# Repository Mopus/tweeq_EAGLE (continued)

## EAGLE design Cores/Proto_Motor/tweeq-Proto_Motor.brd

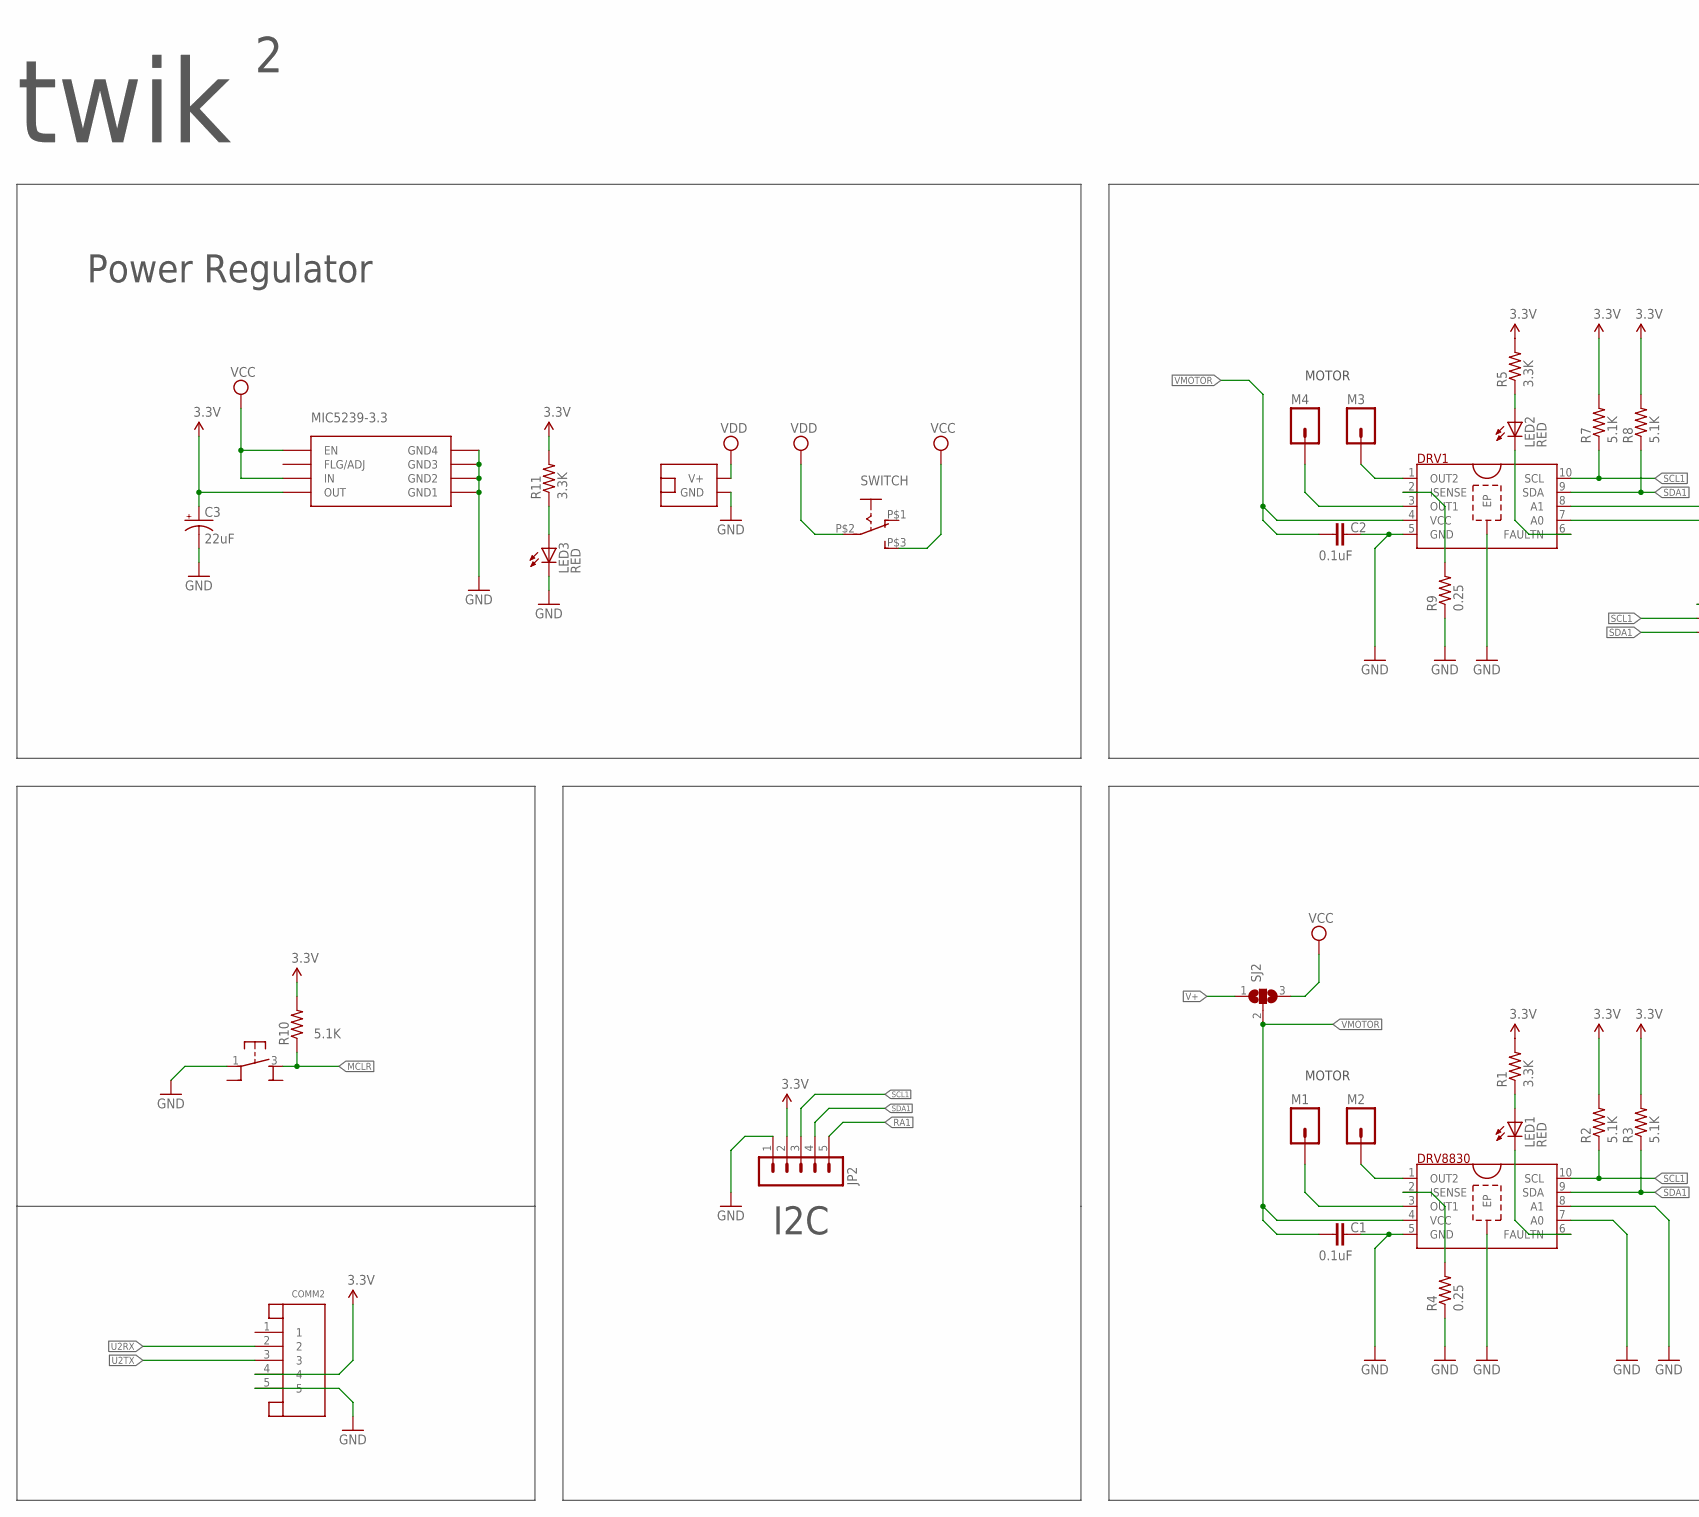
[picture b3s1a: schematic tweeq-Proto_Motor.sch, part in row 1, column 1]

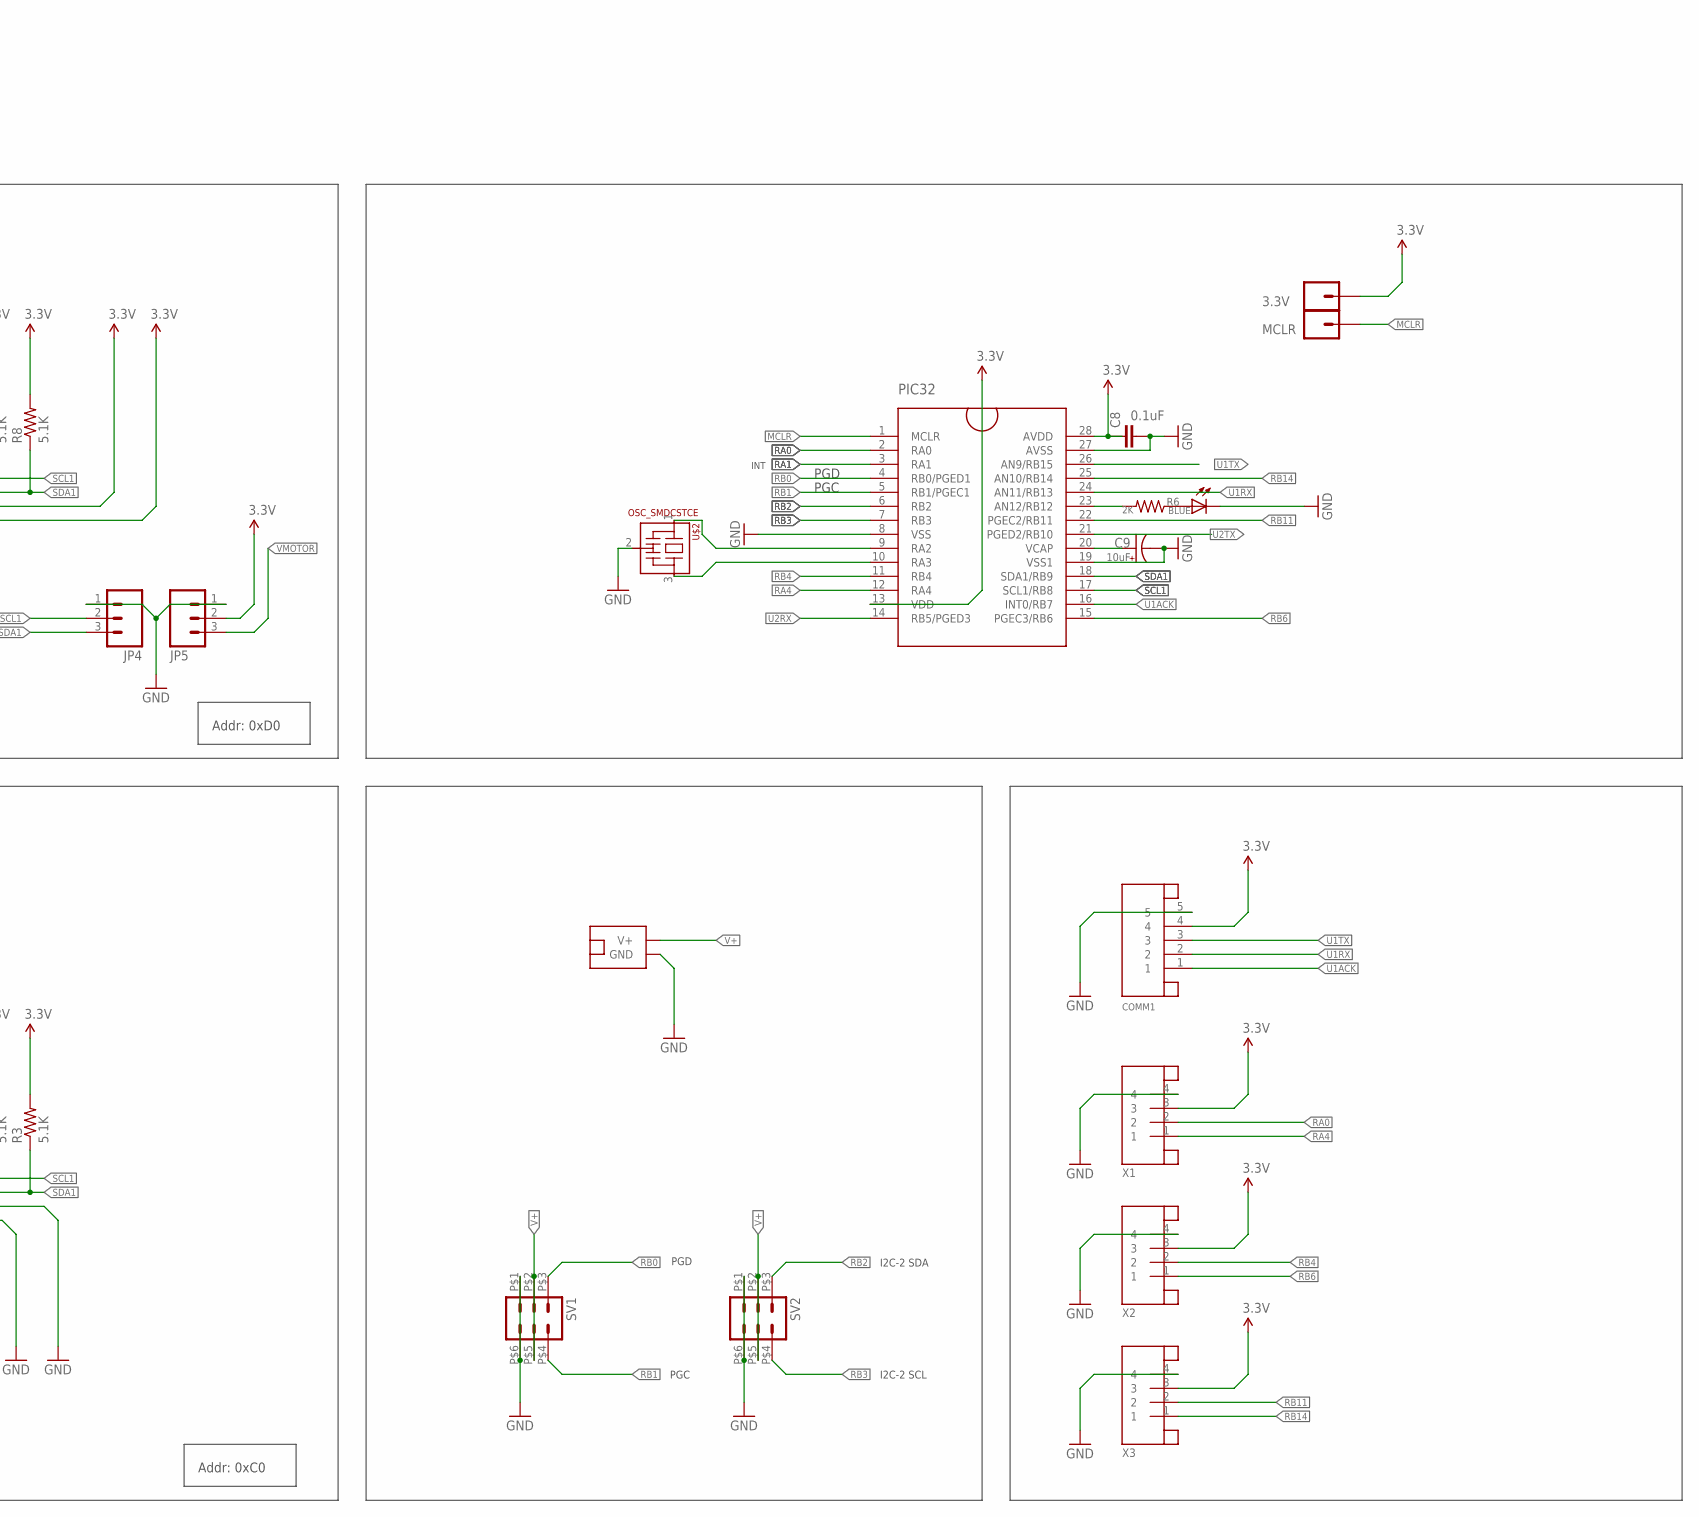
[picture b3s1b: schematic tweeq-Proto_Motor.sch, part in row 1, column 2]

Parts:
3.3V: M01; AISCUBE_1X01_TIGHTFITVIA
C1, C2, C8: 0.1uF; C0402K
C3: 22uF; SMC_B
C9: 10uF; A/3216-18R
COMM1, COMM2: JST-5PINSH; SH1.0-5PIN
DRV1, DRV8830: DRV8830DGQ; MSOP10_POWERPAD
JP2: M05-11.5MM-SMT; 1X05-1.5MM-SMT
JP4, JP5: M03/NS; 1X03_NS
LED1, LED2: RED; CHIPLED_0805
LED3: RED; CHIP-LED0805
M1, M2, M3, M4: M01SQ_NS; 1X01_SQ
MCLR: M01; AISCUBE_1X01_TIGHTFITVIA
MIC5239-3.3: MIC5239-MM; MSOP8
PIC32: PIC32MX_1XX_2XX; SSOP28
PIC_LED: BLUE; CHIP-LED0805
R1, R5, R11: 3.3K; R0402
R2, R3, R7, R8, R10: 5.1K; R0402
R4, R9: 0.25; R0402
R6: 2K; R0402
SJ2: JUMPER_SJ2W; JUMPER_SJ_2
SV1, SV2: M03-2EDGE_PAD; 2X03_EDGEPAD
SWITCH: SLIDE_SWITCH_SMALL
U$2: OSC_SMDCSTCE; CSTCE_RESONATOR_SMD
U$4: PB_MICRO_SMT; PB_SMT_3.5X3X2
U$9, U$10: POWER_CONN/PTH; POWER_CONN_PTH
X1, X2, X3: JST-4PINSH; SH1.0-4PIN

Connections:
3.3V: 3.3V.P$1, C3.+, C8.1, COMM1.4, COMM2.4, DRV1.7 (A0), DRV1.8 (A1), JP2.2, JP5.2, MIC5239-3.3.4 (OUT), PIC32.13 (VDD), PIC32.28 (AVDD), R1.2, R2.2, R3.2, R5.2, R7.2, R8.2, R10.2, R11.2, X1.3, X2.3, X3.3
GND: C1.2, C2.2, C3.-, C8.2, C9.-, COMM1.5, COMM2.5, DRV1.5 (GND), DRV1.EP, DRV8830.5 (GND), DRV8830.7 (A0), DRV8830.8 (A1), DRV8830.EP, JP2.1, JP4.1, JP5.1, LED3.C, MIC5239-3.3.5 (GND1), MIC5239-3.3.6 (GND2), MIC5239-3.3.7 (GND3), MIC5239-3.3.8 (GND4), PIC32.8 (VSS), PIC32.19 (VSS1), PIC32.27 (AVSS), PIC_LED.C, R4.1, R9.1, SV1.P$1 (1), SV1.P$6 (6), SV2.P$1 (1), SV2.P$6 (6), U$2.2 (VSS), U$4.1, U$9.GND, U$10.GND, X1.4, X2.4, X3.4
LED: PIC32.23 (AN12/RB12), R6.2
MCLR: MCLR.P$1, PIC32.1 (MCLR), R10.1, U$4.3 (2)
unnamed: PIC32.9 (RA2), U$2.1
unnamed: PIC_LED.A, R6.1
unnamed: C9.+, PIC32.20 (VCAP)
unnamed: PIC32.10 (RA3), U$2.3
unnamed: DRV8830.6 (FAULTN), LED1.C
unnamed: LED1.A, R1.1
unnamed: DRV8830.1 (OUT2), M2.1
unnamed: DRV8830.3 (OUT1), M1.1
unnamed: DRV8830.2 (ISENSE), R4.2
unnamed: DRV1.6 (FAULTN), LED2.C
unnamed: LED2.A, R5.1
unnamed: DRV1.1 (OUT2), M3.1
unnamed: DRV1.3 (OUT1), M4.1
unnamed: DRV1.2 (ISENSE), R9.2
unnamed: LED3.A, R11.1
RA0: PIC32.2 (RA0), X1.2
RA1: JP2.5, PIC32.3 (RA1)
RA4: PIC32.12 (RA4), X1.1
RB0: PIC32.4 (RB0/PGED1), SV1.P$3 (3)
RB1: PIC32.5 (RB1/PGEC1), SV1.P$4 (4)
RB2: PIC32.6 (RB2), SV2.P$3 (3)
RB3: PIC32.7 (RB3), SV2.P$4 (4)
RB4: PIC32.11 (RB4), X2.2
RB6: PIC32.15 (PGEC3/RB6), X2.1
RB11: PIC32.22 (PGEC2/RB11), X3.2
RB14: PIC32.25 (AN10/RB14), X3.1
SCL1: DRV1.10 (SCL), DRV8830.10 (SCL), JP2.3, JP4.2, PIC32.17 (SCL1/RB8), R2.1, R7.1
SDA1: DRV1.9 (SDA), DRV8830.9 (SDA), JP2.4, JP4.3, PIC32.18 (SDA1/RB9), R3.1, R8.1
U1ACK: COMM1.1, PIC32.16 (INT0/RB7)
U1RX: COMM1.2, PIC32.24 (AN11/RB13)
U1TX: COMM1.3, PIC32.26 (AN9/RB15)
U2RX: COMM2.2, PIC32.14 (RB5/PGED3)
U2TX: COMM2.3, PIC32.21 (PGED2/RB10)
V+: SJ2.1, SV1.P$2 (2), SV1.P$5 (5), SV2.P$2 (2), SV2.P$5 (5), U$10.V+
VCC: MIC5239-3.3.1 (EN), MIC5239-3.3.3 (IN), SJ2.3, SWITCH.P$3 (S)
VDD: SWITCH.P$2, U$9.V+
VMOTOR: C1.1, C2.1, DRV1.4 (VCC), DRV8830.4 (VCC), JP5.3, SJ2.2

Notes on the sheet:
twik
PGC
PGD
INT
MOTOR
Power Regulator
Addr: 0xD0
Addr: 0xC0
I2C
I2C-2 SCL
I2C-2 SDA

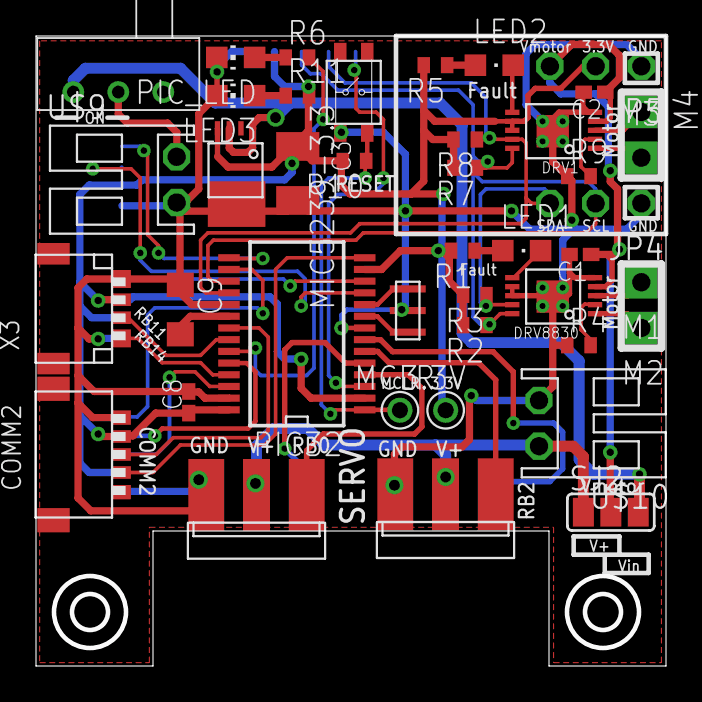
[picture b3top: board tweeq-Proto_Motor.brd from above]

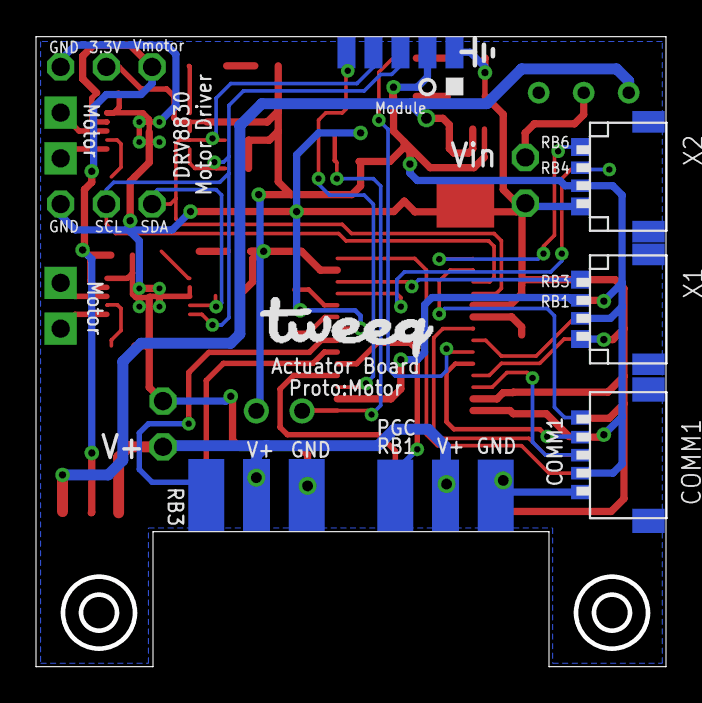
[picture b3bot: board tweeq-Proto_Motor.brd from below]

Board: 2 copper layers, 35.0 x 35.0 mm, 47 parts (5 on the bottom side), 41 nets.

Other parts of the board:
U$1: TWEEQ-LOGO-M

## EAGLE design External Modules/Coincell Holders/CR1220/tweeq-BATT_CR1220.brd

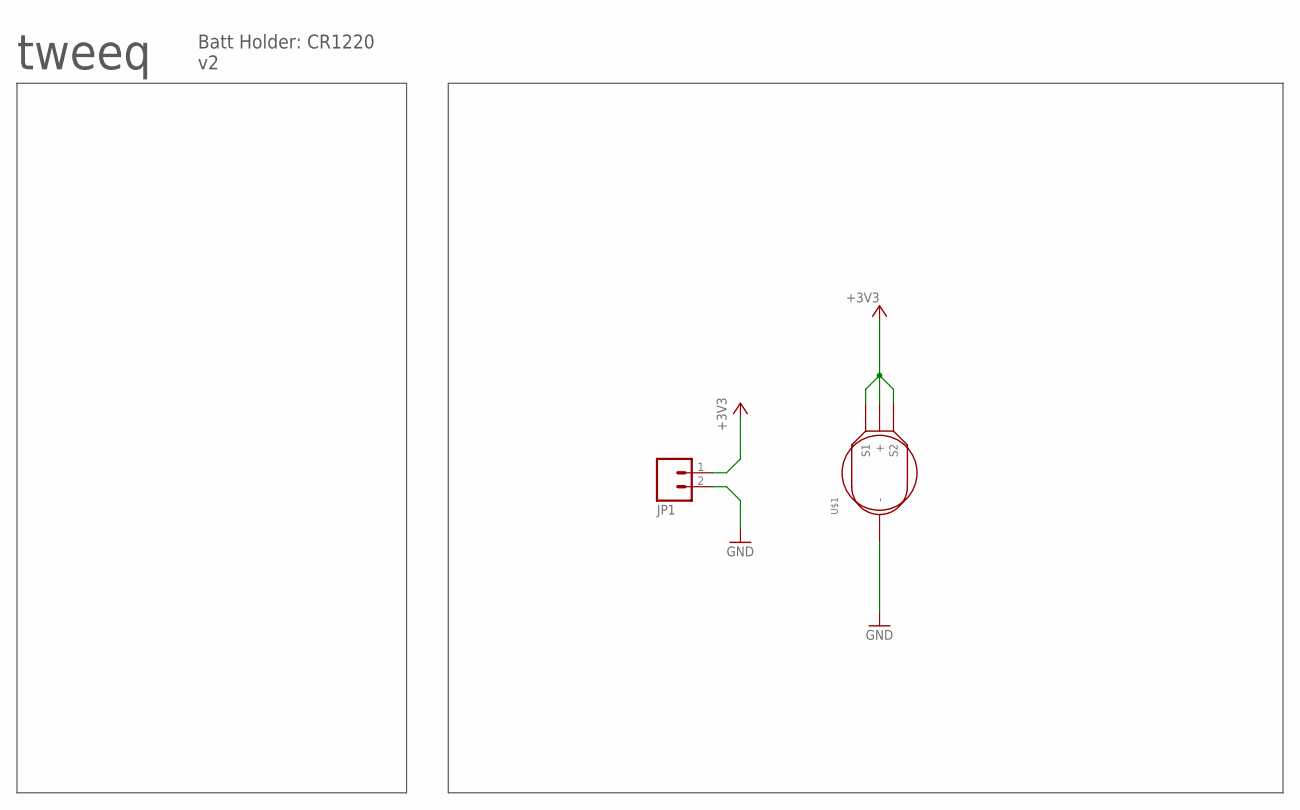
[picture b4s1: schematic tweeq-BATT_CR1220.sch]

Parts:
JP1: M02/SMD_POL; 1X02_SMD_POL
U$1: BATT_HOLDER-CC/CR1220_TH; CR1220_TH

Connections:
+3V3: JP1.1, U$1.+1 (+), U$1.+2 (S2), U$1.P$1 (S1)
GND: JP1.2, U$1.-

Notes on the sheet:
tweeq
Batt Holder: CR1220 v2

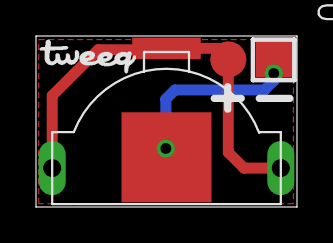
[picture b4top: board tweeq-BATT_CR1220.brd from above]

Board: 2 copper layers, 14.5 x 9.5 mm, 3 parts (0 on the bottom side), 2 nets.

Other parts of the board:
U$2: TWEEQ-LOGO-S

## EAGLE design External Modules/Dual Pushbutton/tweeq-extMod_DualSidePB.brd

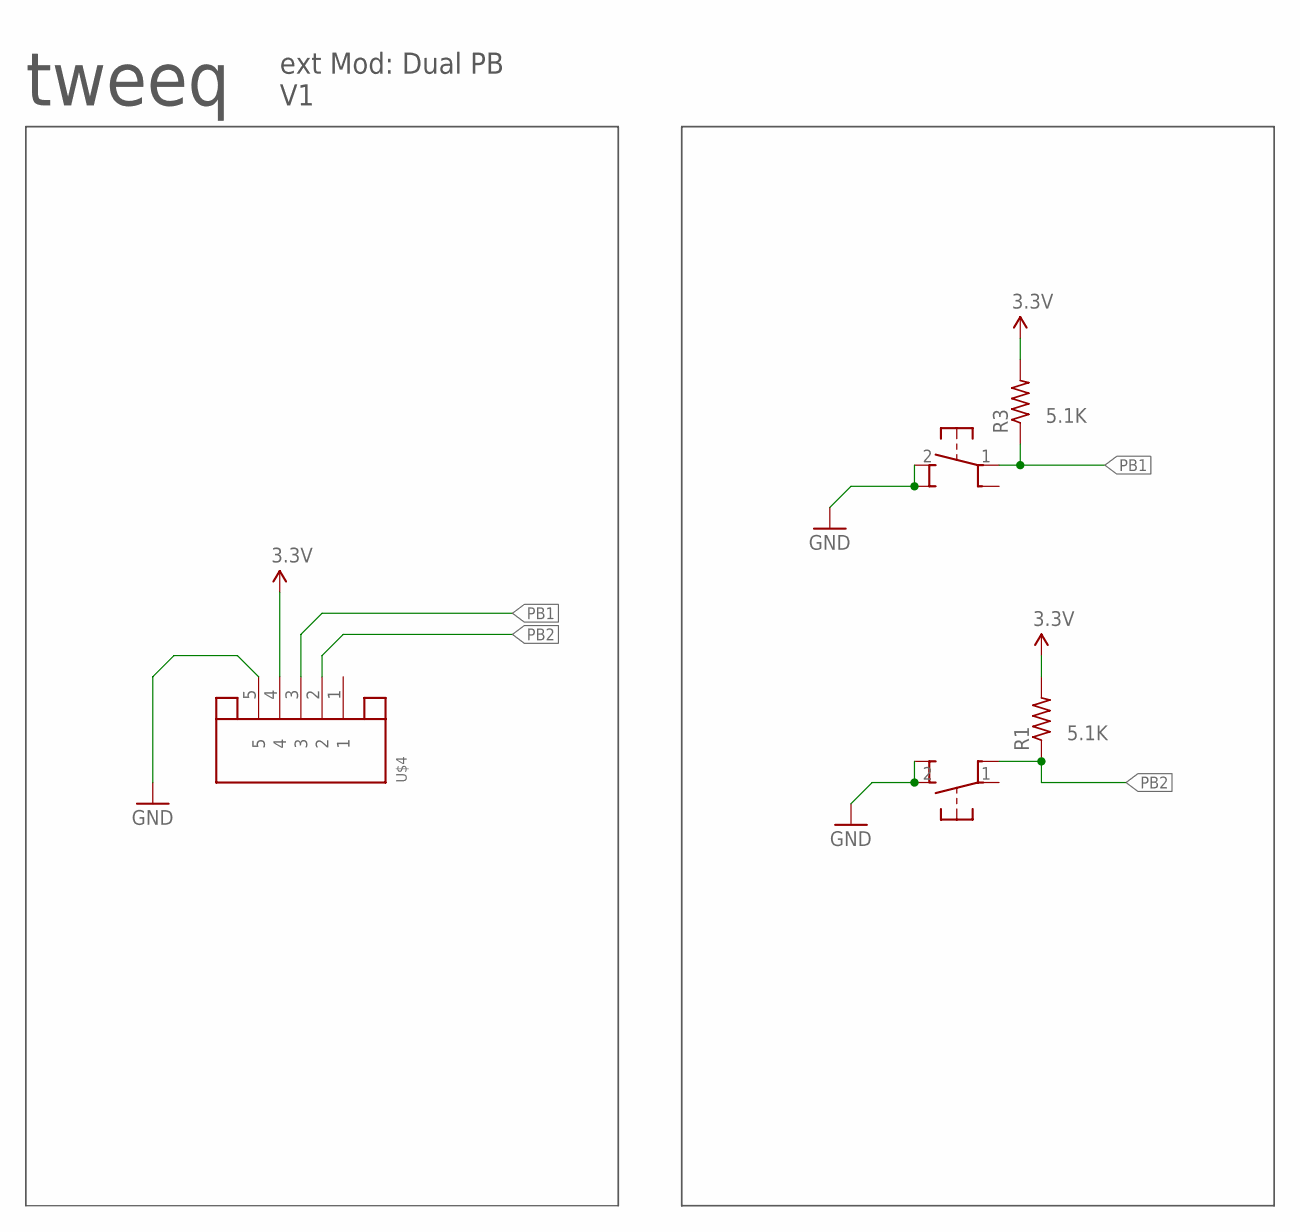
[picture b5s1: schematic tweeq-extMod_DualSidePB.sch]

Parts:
R1, R3: 5.1K; R0402
U$2, U$5: PB_MICRO_SMTRIGHTANGLE; PB_SMT_90D6.2X4.6
U$4: JST-5PINSH; SH1.0-5PIN

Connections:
3.3V: R1.2, R3.2, U$4.4
GND: U$2.2, U$2.2A, U$4.5, U$5.2, U$5.2A
PB1: R3.1, U$4.3, U$5.1
PB2: R1.1, U$2.1A, U$4.2

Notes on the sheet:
tweeq
ext Mod: Dual PB V1

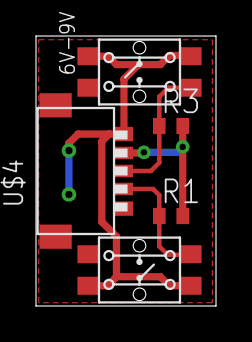
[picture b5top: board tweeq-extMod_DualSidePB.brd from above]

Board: 2 copper layers, 10.0 x 15.0 mm, 6 parts (1 on the bottom side), 4 nets.

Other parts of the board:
U$3: TWEEQ-LOGO-L
